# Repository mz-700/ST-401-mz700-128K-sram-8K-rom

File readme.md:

### Sharp MZ-700 SRAM/ROM Board ###

This is a paged SRAM/ROM board designed for the Sharp MZ-700, and it requires the [Sharp MZ-700 Backplane](https://github.com/mz-700/mz700-backplane) and the [MZ-700 expansion connector board]().

There are 3 versions of this board, each functionning similarly, with the lastest version offering additional features detailed in the branch`readme.md` file. 
This one is the 128K version: 8KB ROM + 128KB SRAM board.

#### How does it work? ####

The Sharp MZ-700 being a 8bit computer, it cannot access more than 64KB of memory. To access this extra memory, it will need to be paged into windows inside its memory map.  
Let's take a look at the 700 memory map:

<sup><sub>From https://original.sharpmz.org</sub></sup>

As we can see, the Sharp MZ-700 has 64KB or DRAM + 2KB of ROM + 4KB of VRAM + some addresses reserved for I/Os.  
To get the full picture of the thing, please read the excellent description Karl-Heinz Mau made on his [site](https://original.sharpmz.org/mz-700/coremain.htm).  

The SRAM/ROM will be mapped at the top of the 700 memory map. From `$E100` to `$FFFF`. Why not from `$E000`? As you can see on this image, the addresses between `$E000` and `$E009` are reserved for I/Os. Actually, the addresses between `$E000` and `$E00F` are reserved for the I/Os. As I am not sure if any other device uses some addresses after `$E00F`. I prefered starting the mapping at `$E100`. We will lose 256 bytes on the first bank, but I guess it is OK.

Talking about banks, the SRAM/ROM are mapped onto 4 banks of 2KB (minus 256 bytes for the 1st one). This means that the SRAM is divided into blocks of 2KB (64 blocks for the 128K version and 256 blocks for the 512K version) and we can choose which of these blocks will be mapped to each of these banks. 

#### The bank addresses are: ####

|Bank #|Start Address|End Address|
|:----:|-------------|-----------|
|0|$E100|$E7FF|
|1|$E800|$EFFF|
|2|$F000|$F7FF|
|3|$F800|$FFFF|

#### The Registers ####

Use the DIP switch on the left of the board to select the base address of the registers. I will call it `BaseAddr`. All the registers are write-only.

|Register|IO Port|Description|
|---|--------|-----------|
|Bank0_block|`BaseAddr`|# of the 2KB SRAM memory block that will be mapped to bank #0|
|Bank1_block|`BaseAddr`+1| # of the 2KB SRAM memory block that will be mapped to bank #1|
|Bank2_block|`BaseAddr`+2| # of the 2KB SRAM memory block that will be mapped to bank #2|
|Bank3_block|`BaseAddr`+3| # of the 2KB SRAM memory block that will be mapped to bank #3|
|Banks_selection|`BaseAddr`+4| 4 bits to choose if the bank will be mapped to ROM (0) or SRAM (1) - 0 by default|
|Board_disable|`BaseAddr`+5| 0 or 1: disable the board altogether - 0 by default (enabled)|

#### Example ####

```
BaseAddr        EQU $A0    ; <- value set by the DIP switches
Bank0_block     EQU BaseAddr
Bank1_block     EQU BaseAddr+1
Bank2_block     EQU BaseAddr+2
Bank3_block     EQU BaseAddr+3
Banks_selection EQU BaseAddr+4
Board_disable   EQU BaseAddr+5

LD  A,10                ; SRAM block #10 ( from SRAM $2800 (10*2KB) to $29FF (10*2KB + 2KB) )
OUT (Bank2_block),A     ; The addresses $F000->$F7FF will point to SRAM block #10
LD  A,%0010             ; 
OUT (Banks_selection),A ; The block #2 will point to SRAM, the others to ROM
LD  A,1
OUT (Board_disable),A   ; The board is disabled
LD  A,0
OUT (Board_disable),A   ; The board is enabled
```

#### When is the board disabled? ####

The board can be disabled with the `Board_disable` register. There are other cases when the board is disabled automatically. As explained in Karl-Heinz's page, the MZ-700 memory layout can change by using the I/O ports $E0 to $E6. This is a table copied from the page. It shows how the memory layout changes by using these ports:

|port#|	$0000 - $0FFF |	$D000 - $FFFF|
| ----|-|-|
|$E0 |	RAM |	no action|
|$E1| 	no action |	RAM|
|$E2 |	ROM| 	no action|
|$E3 |	no action |	V-RAM and I/O ports|
|$E4 |	ROM| 	V-RAM and I/O ports|
|$E5 |	no action |	locked|
|$E6 |	no action |	unlock locked area by $E5 |

As we can see, after `OUT ($E1),A`, the top of the memory is used by the internal DRAM. The board is then disabled to avoid any conflict. The board is then automatically enabled when a `OUT ($E3),A` or `OUT ($E4),A` occurs. The board is also disabled after `OUT ($E5),A`. This locks the top of the memory, meaning that any access to the VRAM or the I/O ports won't work until unlocked (with $E6 or $E4).  
Technically, there is no conflict with the board when the upper memory is locked but it then requires some memory switching each time we want to access to the video or the i/o ports. If this is acceptable, it is easy to update the CPLD code to comment out this test and leave the board active even when the upper memory is locked.

The LED is ON when the board is enabled. OFF when disabled.

### Building the board ###

The board uses an `ATF1502AS` CPLD. This chip requires a specific programmer: The ATDH1150USB. Unfortunately, it is not cheap ($90). 

Here is the BOM:

|Ref|Name|Description|Seller|Seller Reference|Comments|
|---|---|---|---|--|--|
|U1|ATF1502AS|CPLD|[Mouser](https://www.mouser.com/ProductDetail/556-AF1502AS10JU44)|556-AF1502AS10JU44 |  |
|U1|Socket|PLCC44 Socket|[Mouser](https://www.mouser.com/ProductDetail/737-PLCC-44-AT)|737-PLCC-44-AT|
|U2|74HCT688|8 bit comparator|[Mouser](https://www.mouser.com/ProductDetail/595-CD74HCT688EE4)|595-CD74HCT688EE4 |
|U3-U4|74LS670|4x4 Register|[Mouser](https://www.mouser.com/ProductDetail/595-SN74LS670N)|595-SN74LS670N |LS because the HCT is really expensive|
|U5|AS6C1008|128KB SRAM|[Mouser](https://www.mouser.com/ProductDetail/913-AS6C1008-55PCN)|913-AS6C1008-55PCN |
|U6|28C64|8KB EEPROM|[Mouser](https://www.mouser.com/ProductDetail/556-AT28C64B15PU)|556-AT28C64B15PU|
|C1-C9|Capacitor|0.1uF 50V +/-10% 5mm Decoupling capacitor|[Mouser](https://www.mouser.com/ProductDetail/594-K104K15X7RF53H5G)|594-K104K15X7RF53H5G |
|R1|Resistor|300 ohm|[Mouser](https://www.mouser.com/ProductDetail/594-MBE04140C3300FC1)|594-MBE04140C3300FC1 |
|D1|LED|5mm LED|[Mouser](https://www.mouser.com/ProductDetail/%20593-LTH5MM12VFR4100)|593-LTH5MM12VFR4100 |
|J1|connector|Shrouded 2x5 male connector|[Mouser](https://www.mouser.com/ProductDetail/200-TST10501GD)|200-TST10501GD |
|J2|connector|1x34 angled 2.54mm pin header|[Mouser](https://www.mouser.com/ProductDetail/649-78938-434HLF)|649-78938-434HLF |
|RN1|Resistor|5x10K Resistor Network|[Mouser](https://www.mouser.com/ProductDetail/652-4606X-1LF-10K)|652-4606X-1LF-10K 
|SW1|Switch|5x DIP Switch|[Mouser](https://www.mouser.com/ProductDetail/774-1945MST)|774-1945MST
|||CPDL Programmer|[Mouser](https://www.mouser.com/ProductDetail/556-ATDH1150USB)|556-ATDH1150USB|

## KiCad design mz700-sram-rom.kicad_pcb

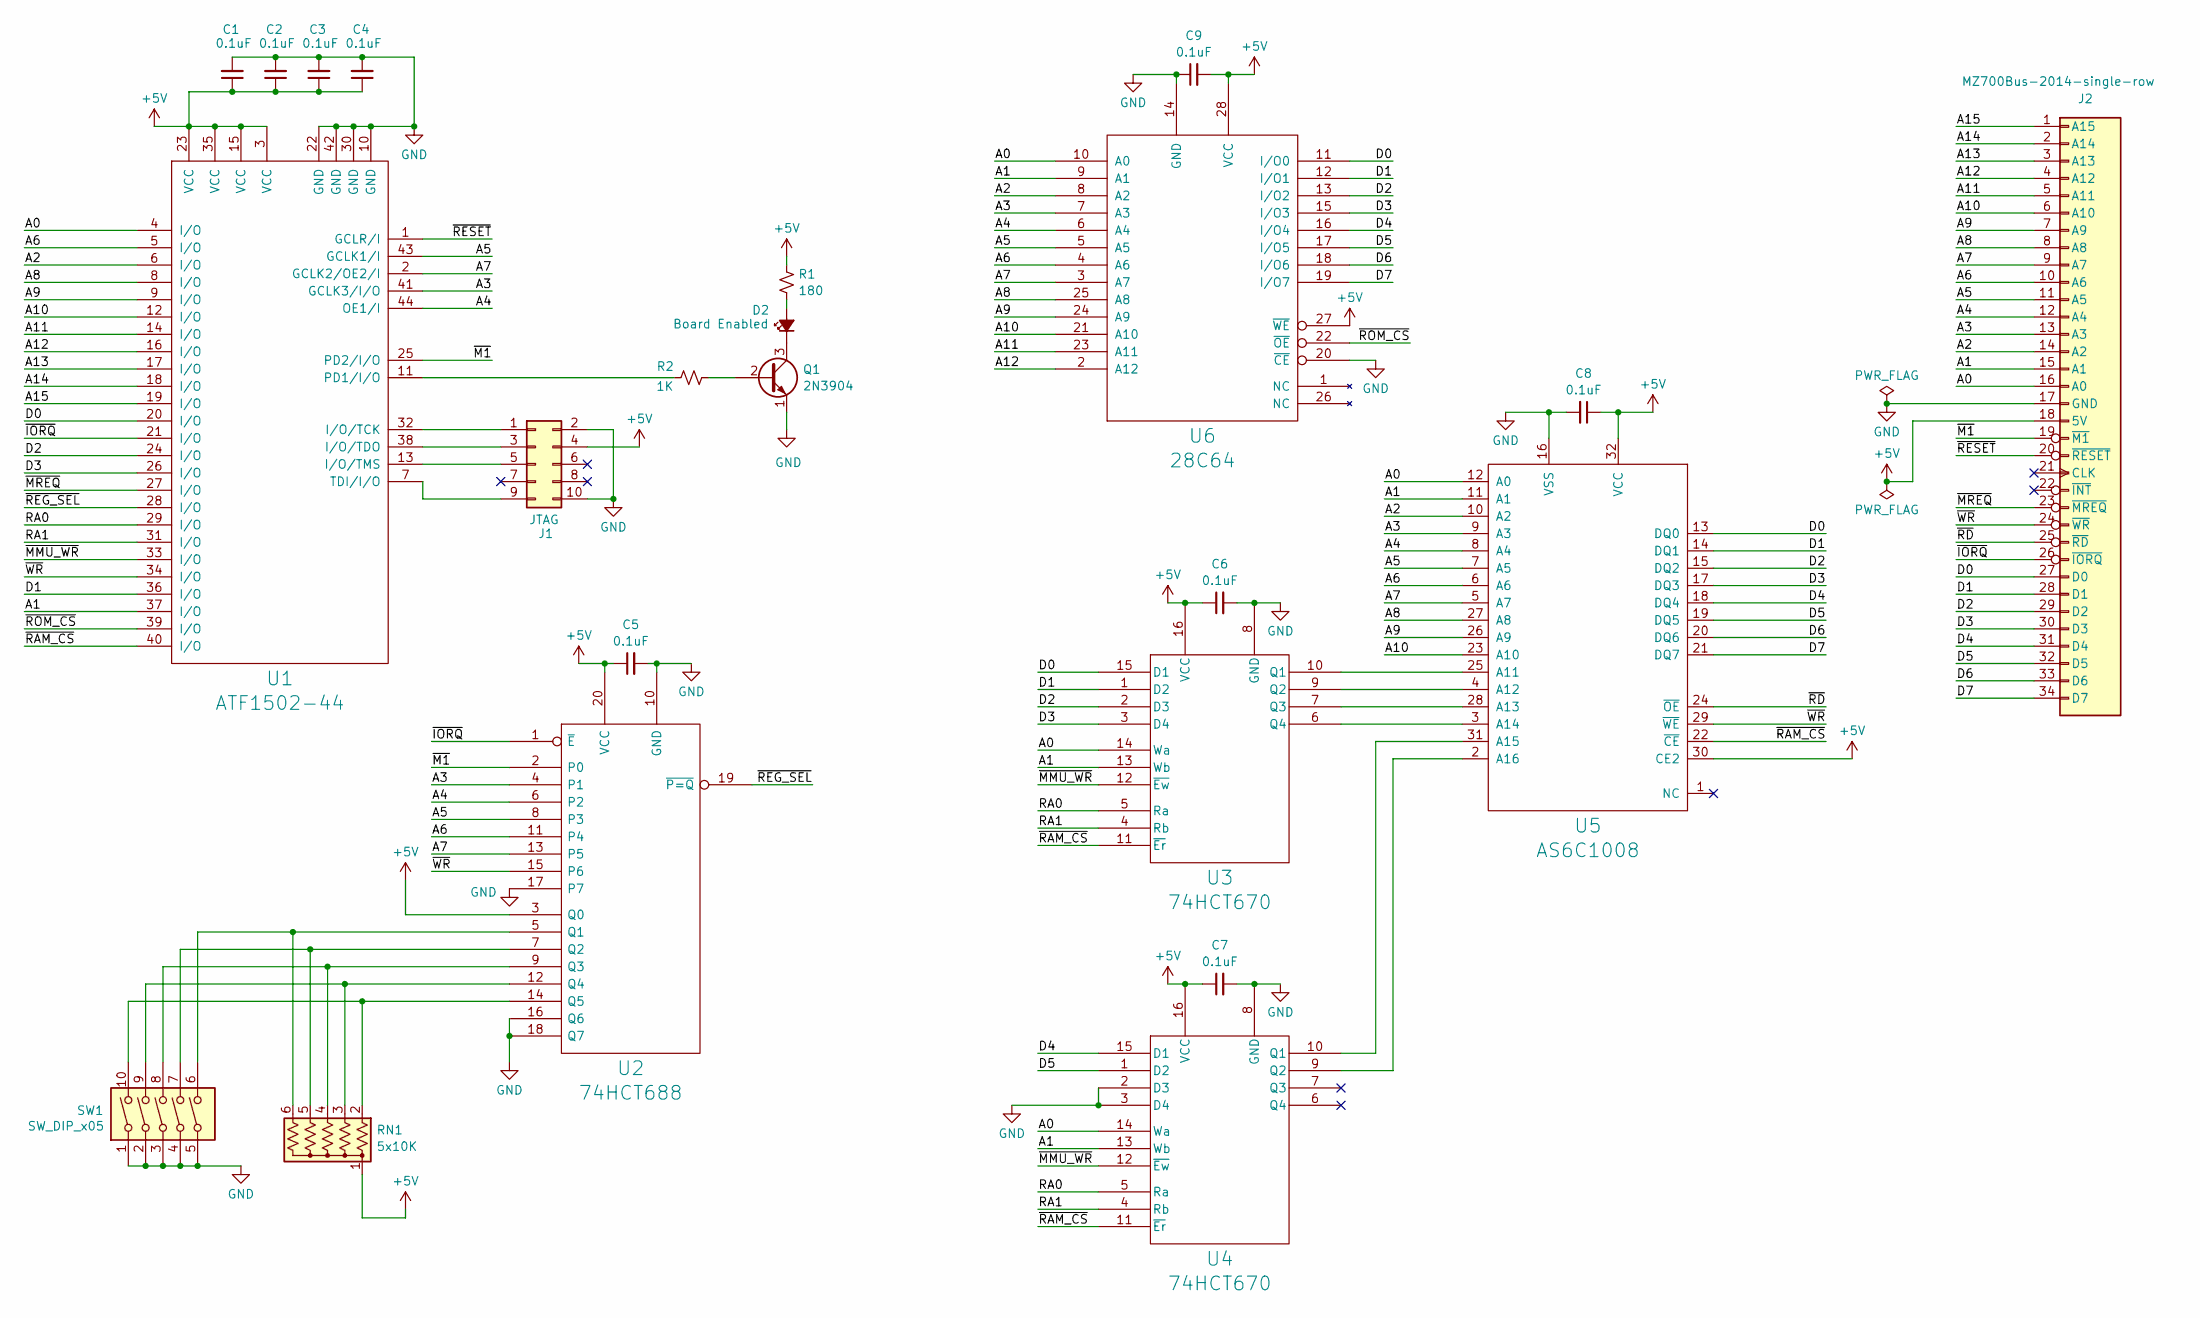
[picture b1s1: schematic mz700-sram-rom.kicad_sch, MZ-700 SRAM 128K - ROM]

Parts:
C1, C2, C3, C4, C5, C6, C7, C8, C9: 0.1uF; C_Disc_D5.0mm_W2.5mm_P5.00mm
D2: Board Enabled; LED_D3.0mm
J1: JTAG; PinHeader_2x05_P2.54mm_Vertical
J2: MZ700Bus-2014-single-row; PinSocket_1x34_P2.54mm_Vertical
Q1: 2N3904; TO-92_Inline
R1: 180; R_Axial_DIN0204_L3.6mm_D1.6mm_P7.62mm_Horizontal
R2: 1K; R_Axial_DIN0204_L3.6mm_D1.6mm_P7.62mm_Horizontal
RN1: 5x10K; R_Array_SIP6
SW1: SW_DIP_x05; DIP-10_W7.62mm_Socket_LongPads
U1: ATF1502-44; PLCC-44_THT-Socket
U2: 74HCT688; DIP-20_W7.62mm_Socket_LongPads
U3, U4: 74HCT670; DIP-16_W7.62mm_Socket_LongPads
U5: AS6C1008; DIP-32_W15.24mm_Socket_LongPads
U6: 28C64; DIP-28_W15.24mm_Socket_LongPads

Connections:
+5V: C1.1, C2.1, C3.1, C4.1, C5.1, C6.1, C7.1, C8.1, C9.2, J1.4, J2.18 (5V), R1.1, RN1.1 (common), U1.3 (VCC), U1.15 (VCC), U1.23 (VCC), U1.35 (VCC), U2.3 (Q0), U2.20 (VCC), U3.16 (VCC), U4.16 (VCC), U5.30 (CE2), U5.32 (VCC), U6.27 (~WE), U6.28 (VCC)
/A0: J2.16 (A0), U1.4 (I/O), U3.14 (Wa), U4.14 (Wa), U5.12 (A0), U6.10 (A0)
/A1: J2.15 (A1), U1.37 (I/O), U3.13 (Wb), U4.13 (Wb), U5.11 (A1), U6.9 (A1)
/A2: J2.14 (A2), U1.6 (I/O), U5.10 (A2), U6.8 (A2)
/A3: J2.13 (A3), U1.41 (GCLK3/I/O), U2.4 (P1), U5.9 (A3), U6.7 (A3)
/A4: J2.12 (A4), U1.44 (OE1/I), U2.6 (P2), U5.8 (A4), U6.6 (A4)
/A5: J2.11 (A5), U1.43 (GCLK1/I), U2.8 (P3), U5.7 (A5), U6.5 (A5)
/A6: J2.10 (A6), U1.5 (I/O), U2.11 (P4), U5.6 (A6), U6.4 (A6)
/A7: J2.9 (A7), U1.2 (GCLK2/OE2/I), U2.13 (P5), U5.5 (A7), U6.3 (A7)
/A8: J2.8 (A8), U1.8 (I/O), U5.27 (A8), U6.25 (A8)
/A9: J2.7 (A9), U1.9 (I/O), U5.26 (A9), U6.24 (A9)
/A10: J2.6 (A10), U1.12 (I/O), U5.23 (A10), U6.21 (A10)
/A11: J2.5 (A11), U1.14 (I/O), U6.23 (A11)
/A12: J2.4 (A12), U1.16 (I/O), U6.2 (A12)
/A13: J2.3 (A13), U1.17 (I/O)
/A14: J2.2 (A14), U1.18 (I/O)
/A15: J2.1 (A15), U1.19 (I/O)
/D0: J2.27 (D0), U1.20 (I/O), U3.15 (D1), U5.13 (DQ0), U6.11 (I/O0)
/D1: J2.28 (D1), U1.36 (I/O), U3.1 (D2), U5.14 (DQ1), U6.12 (I/O1)
/D2: J2.29 (D2), U1.24 (I/O), U3.2 (D3), U5.15 (DQ2), U6.13 (I/O2)
/D3: J2.30 (D3), U1.26 (I/O), U3.3 (D4), U5.17 (DQ3), U6.15 (I/O3)
/D4: J2.31 (D4), U4.15 (D1), U5.18 (DQ4), U6.16 (I/O4)
/D5: J2.32 (D5), U4.1 (D2), U5.19 (DQ5), U6.17 (I/O5)
/D6: J2.33 (D6), U5.20 (DQ6), U6.18 (I/O6)
/D7: J2.34 (D7), U5.21 (DQ7), U6.19 (I/O7)
/RA0: U1.29 (I/O), U3.5 (Ra), U4.5 (Ra)
/RA1: U1.31 (I/O), U3.4 (Rb), U4.4 (Rb)
/~IORQ: J2.26 (~IORQ), U1.21 (I/O), U2.1 (~E)
/~M1: J2.19 (~M1), U1.25 (PD2/I/O), U2.2 (P0)
/~MMU_WR: U1.33 (I/O), U3.12 (~Ew), U4.12 (~Ew)
/~MREQ: J2.23 (~MREQ), U1.27 (I/O)
/~RAM_CS: U1.40 (I/O), U3.11 (~Er), U4.11 (~Er), U5.22 (~CE)
/~RD: J2.25 (~RD), U5.24 (~OE)
/~REG_SEL: U1.28 (I/O), U2.19 (~P=Q)
/~RESET: J2.20 (~RESET), U1.1 (GCLR/I)
/~ROM_CS: U1.39 (I/O), U6.22 (~OE)
/~WR: J2.24 (~WR), U1.34 (I/O), U2.15 (P6), U5.29 (~WE)
GND: C1.2, C2.2, C3.2, C4.2, C5.2, C6.2, C7.2, C8.2, C9.1, J1.2, J1.10, J2.17 (GND), Q1.1 (E), SW1.1, SW1.2, SW1.3, SW1.4, SW1.5, U1.10 (GND), U1.22 (GND), U1.30 (GND), U1.42 (GND), U2.10 (GND), U2.16 (Q6), U2.17 (P7), U2.18 (Q7), U3.8 (GND), U4.2 (D3), U4.3 (D4), U4.8 (GND), U5.16 (VSS), U6.14 (GND), U6.20 (~CE)
unnamed: D2.2 (A), R1.2
unnamed: D2.1 (K), Q1.3 (C)
unnamed: J1.1, U1.32 (I/O/TCK)
unnamed: J1.3, U1.38 (I/O/TDO)
unnamed: J1.5, U1.13 (I/O/TMS)
unnamed: J1.9, U1.7 (TDI/I/O)
unnamed: Q1.2 (B), R2.2
unnamed: RN1.2 (R1), SW1.10, U2.14 (Q5)
unnamed: RN1.3 (R2), SW1.9, U2.12 (Q4)
unnamed: RN1.4 (R3), SW1.8, U2.9 (Q3)
unnamed: RN1.5 (R4), SW1.7, U2.7 (Q2)
unnamed: RN1.6 (R5), SW1.6, U2.5 (Q1)
unnamed: R2.1, U1.11 (PD1/I/O)
unnamed: U3.10 (Q1), U5.25 (A11)
unnamed: U3.9 (Q2), U5.4 (A12)
unnamed: U3.7 (Q3), U5.28 (A13)
unnamed: U3.6 (Q4), U5.3 (A14)
unnamed: U4.10 (Q1), U5.31 (A15)
unnamed: U4.9 (Q2), U5.2 (A16)

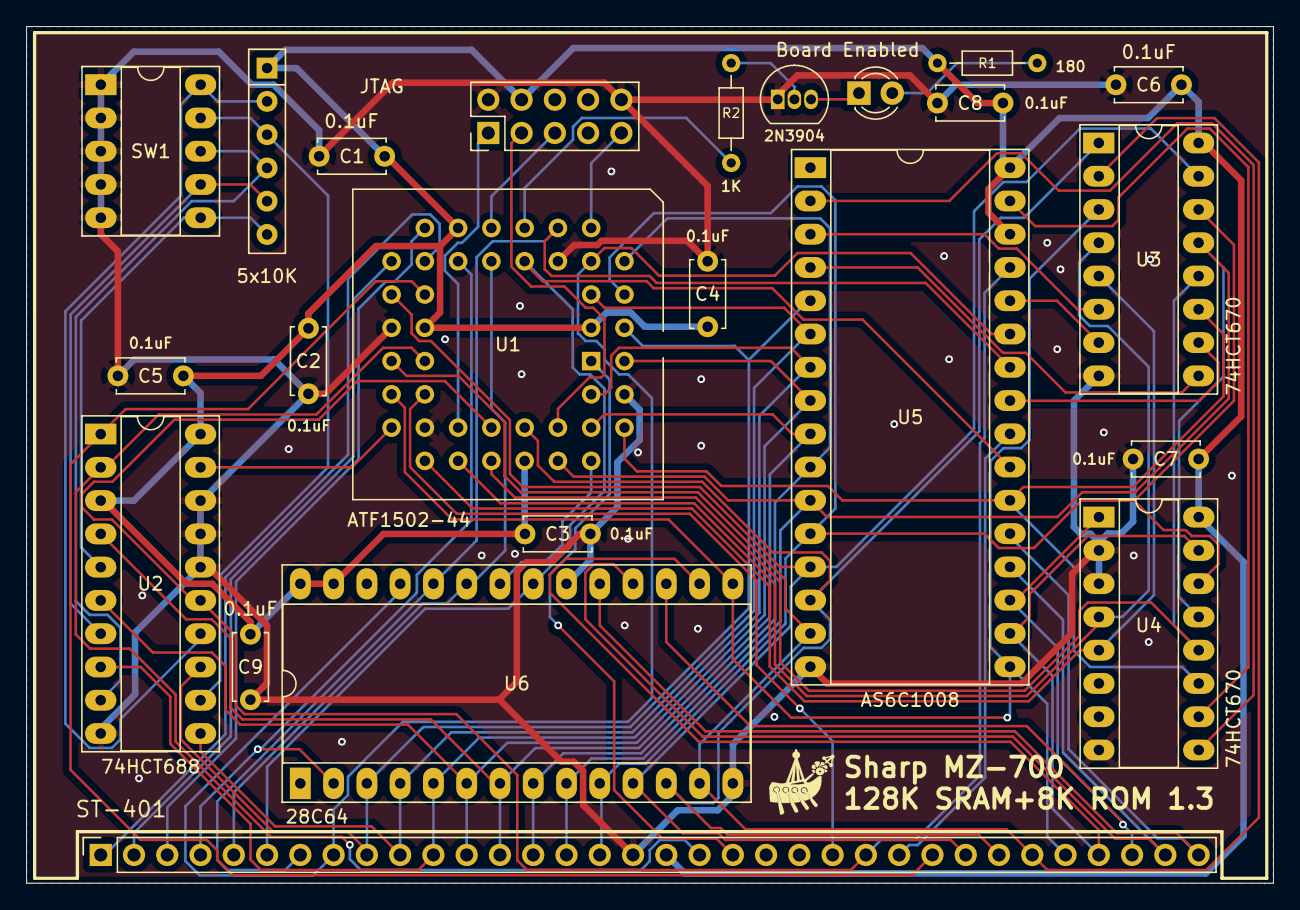
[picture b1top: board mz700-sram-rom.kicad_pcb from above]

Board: 2 copper layers, 95.2 x 65.4 mm, 24 parts (0 on the bottom side), 57 nets.

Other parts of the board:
Ref**: Val**; logo.cdr

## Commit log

2024-07-05 8KB ROM + 128KB SRAM Board
2024-07-08 1.3
    Added logic to disable the board is $D000->$FFFF is locked ($E5) or DRAM ($E1)
2024-07-09 renamed PLD file
2024-07-10 updated schematics pdf + pld
2024-07-30 added board id
2024-08-17 cleanup
2024-08-21 replaced LED from cpld with transistor
